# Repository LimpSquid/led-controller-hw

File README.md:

# Next revision
- Pull-ups (10k) on TLC5940 outputs.
- Pull-ups on MOSFET gates need to be lowered to 1k.
- Add 47nF capacitors on drain (output) of MOSFETs to reduce noise.

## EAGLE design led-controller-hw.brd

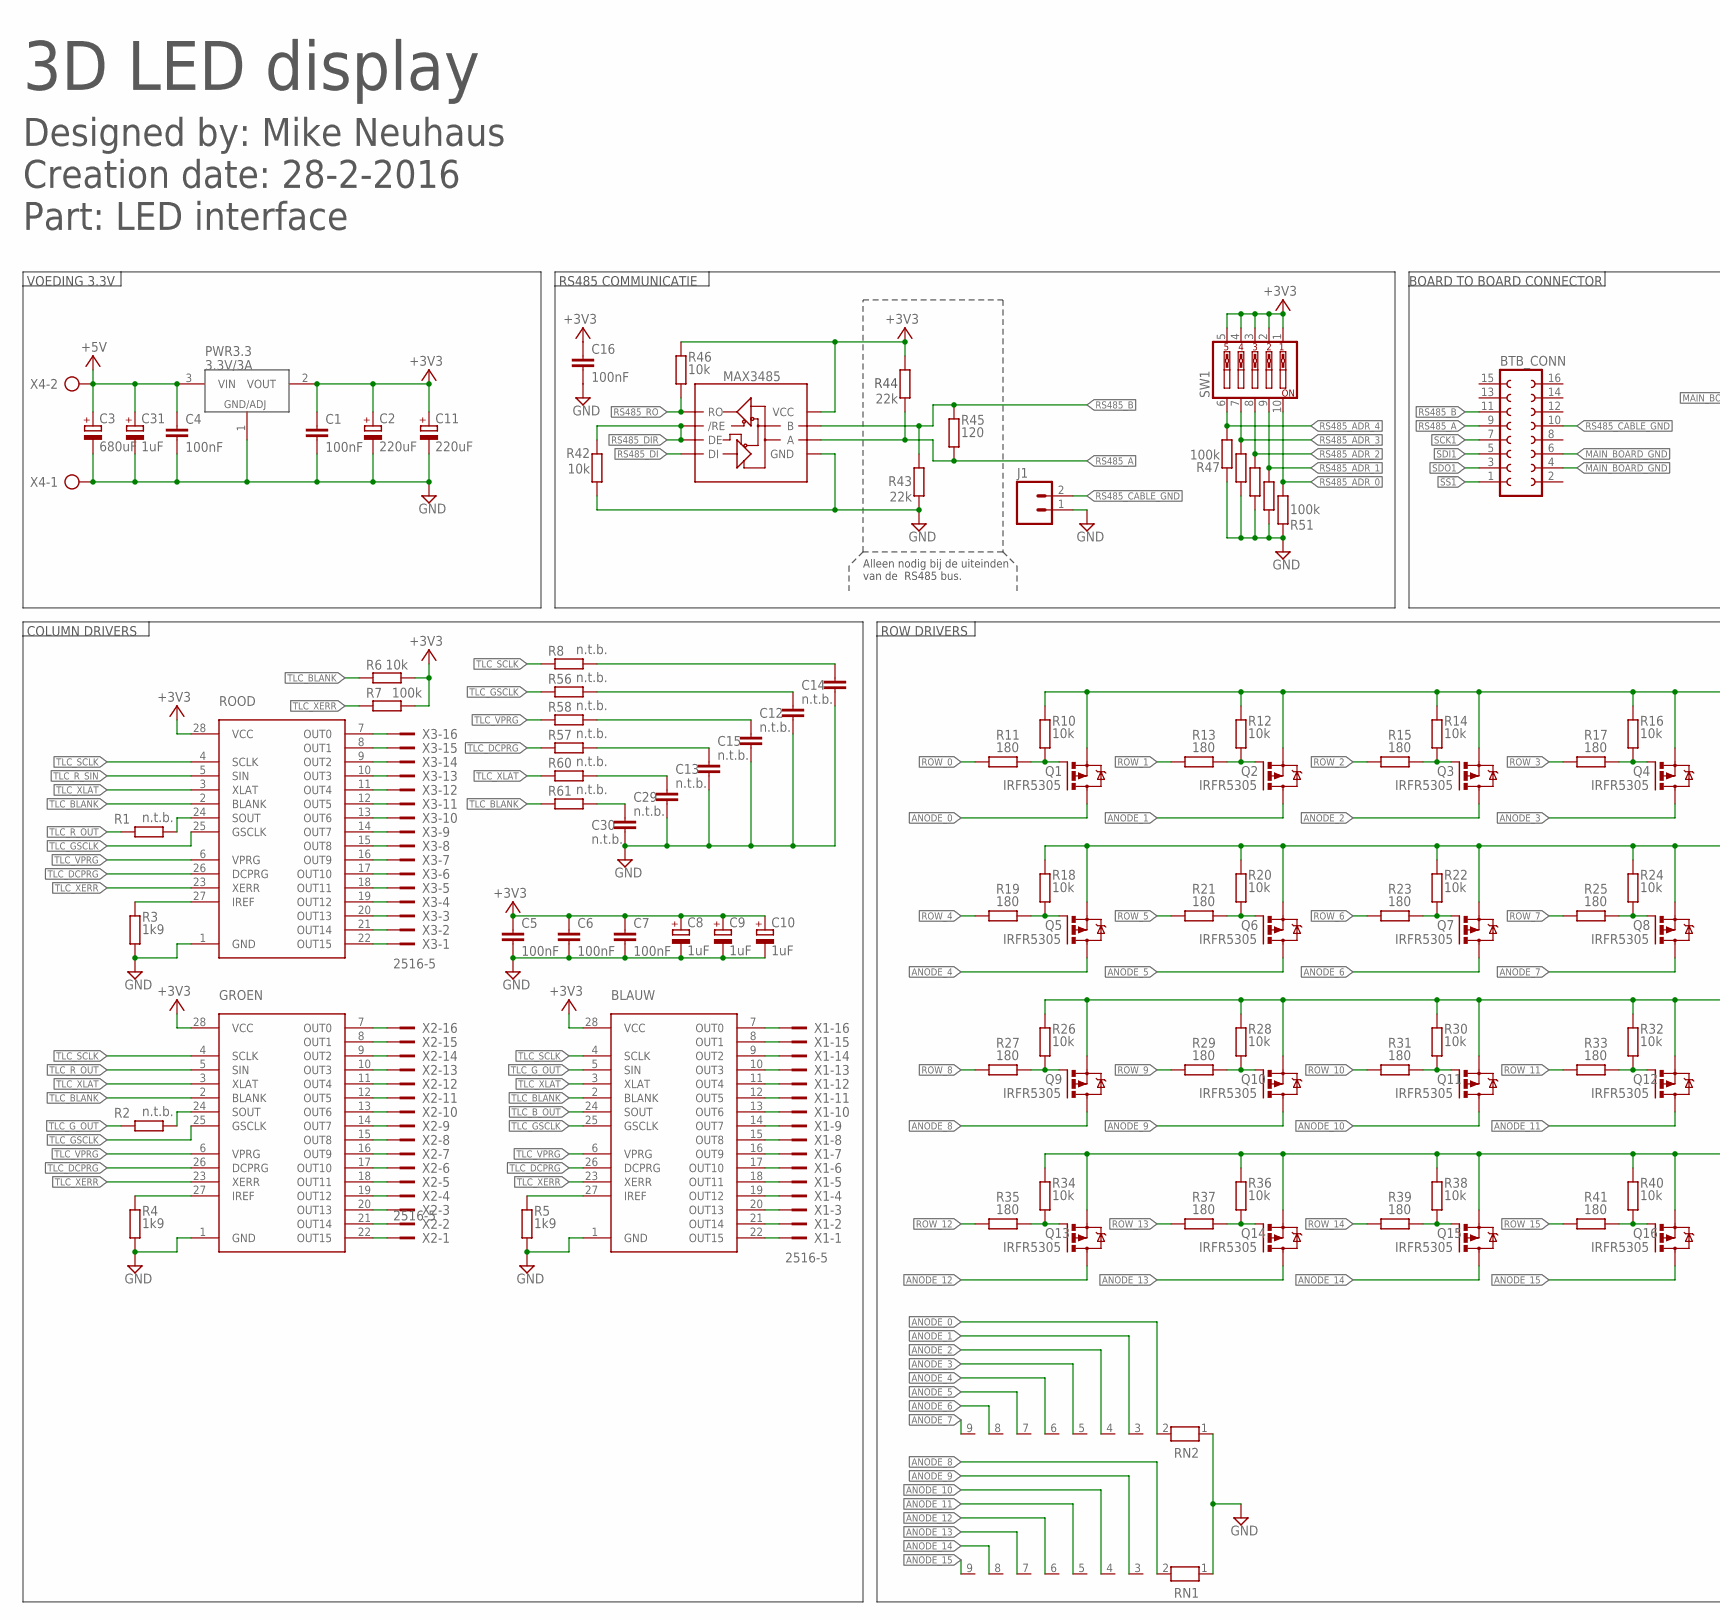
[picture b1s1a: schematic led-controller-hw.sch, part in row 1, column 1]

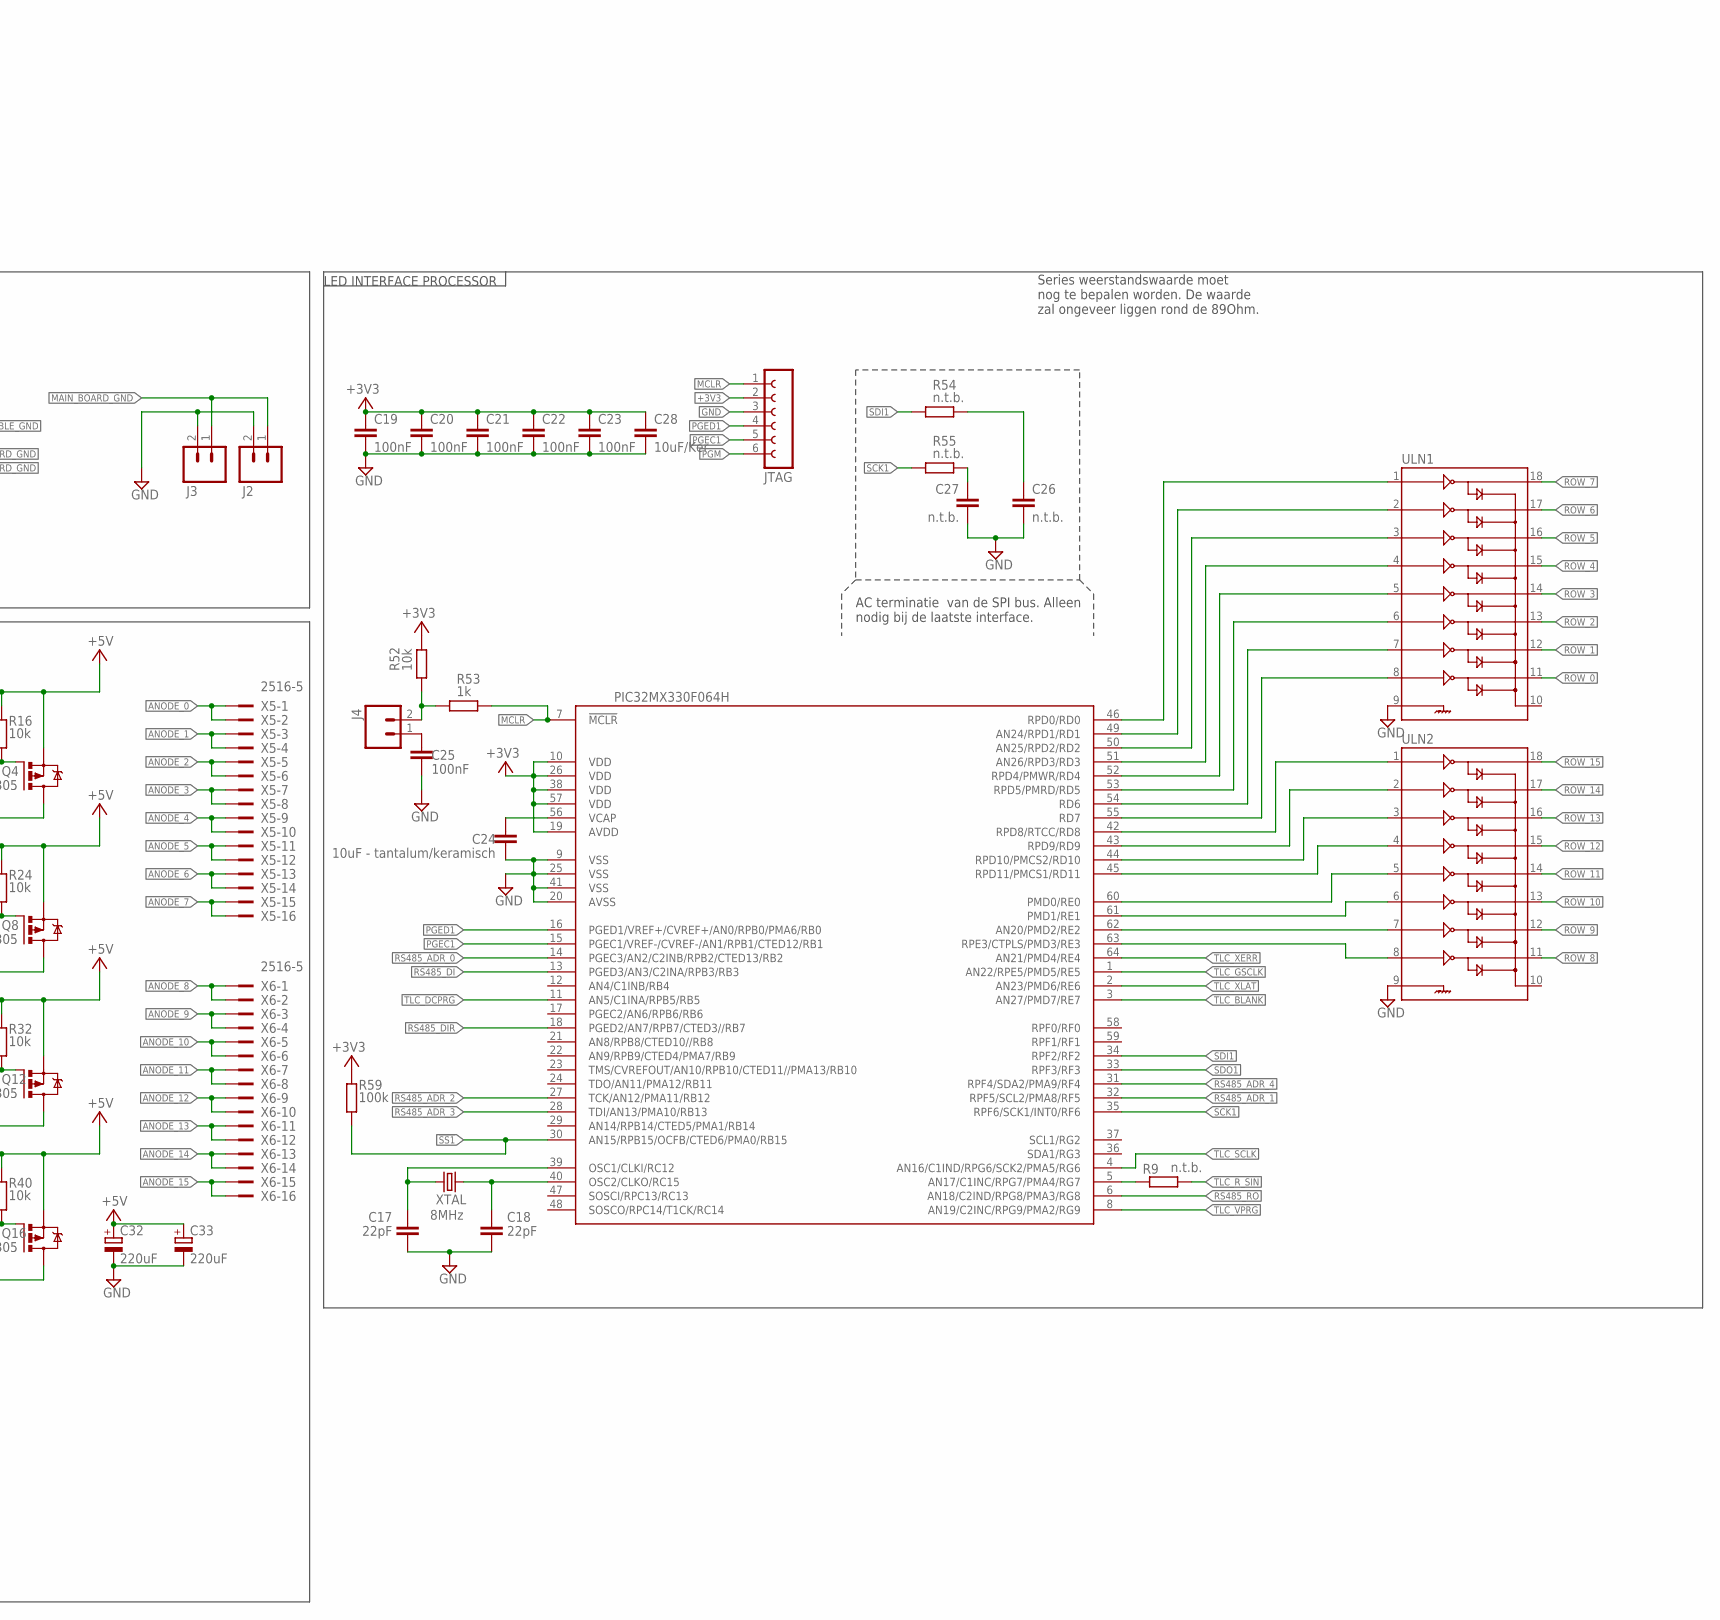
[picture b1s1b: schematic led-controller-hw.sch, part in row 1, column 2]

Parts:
BLAUW: TLC5940PWPR; TSSOP-28-PWP
BTB_CONN: FE08-2W
C1, C4, C5, C6, C7, C16, C19, C20, C21, C22, C23, C25: 100nF; C0805
C2, C11, C32, C33: 220uF; E2,5-6E
C3: 680uF; CPOL_EU10-27
C8, C9, C10, C31: 1uF; E2,5-5
C12, C13, C14, C15, C26, C27, C29, C30: n.t.b.; C0805
C17, C18: 22pF; C0805
C24: 10uF - tantalum/keramisch; C0805
C28: 10uF/Ker; C0805
GROEN: TLC5940PWPR; TSSOP-28-PWP
J1, J2, J3, J4: M02LOCK; 1X02_LOCK
JTAG: FE06-1; FE06
MAX3485: RS485SOIC; SO08
PIC32MX330F064H: PIC32MX330F064H; TQFP-64-10
PWR3.3: 3.3V/3A; TO-220
Q1, Q2, Q3, Q4, Q5, Q6, Q7, Q8, Q9, Q10, Q11, Q12, Q13, Q14, Q15, Q16: IRFR5305; D-PAK_TO252AA
R1, R2, R8, R9, R54, R55, R56, R57, R58, R60, R61: n.t.b.; M0805
R3, R4, R5: 1k9; M0805
R6, R10, R12, R14, R16, R18, R20, R22, R24, R26, R28, R30, R32, R34, R36, R38, R40, R42, R46, R52: 10k; M0805
R7, R47, R48, R49, R50, R51, R59: 100k; M0805
R11, R13, R15, R17, R19, R21, R23, R25, R27, R29, R31, R33, R35, R37, R39, R41: 180; M0805
R43, R44: 22k; M0805
R45: 120; M0805
R53: 1k; M0805
RN1, RN2: RN08; RN-9
ROOD: TLC5940PWPR; TSSOP-28-PWP
SW1: SW_DIP-5; EDG-05
ULN1, ULN2: ULN2803SOICW; SO18L
X1, X2, X3, X5, X6: 2516-5; PAK100/2500-5-16
X4: AK500/2-H
XTAL: 8MHz; CSM-7X-DU

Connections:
!SS1: BTB_CONN.1, PIC32MX330F064H.30 (AN15/RPB15/OCFB/CTED6/PMA0/RB15), R59.2
+3V3: BLAUW.28 (VCC), C1.1, C2.+, C5.1, C6.1, C7.1, C8.+, C9.+, C10.+, C11.+, C16.1, C19.1, C20.1, C21.1, C22.1, C23.1, C28.1, GROEN.28 (VCC), JTAG.2, MAX3485.8 (VCC), PIC32MX330F064H.10 (VDD), PIC32MX330F064H.19 (AVDD), PIC32MX330F064H.26 (VDD), PIC32MX330F064H.38 (VDD), PIC32MX330F064H.57 (VDD), PWR3.3.2 (VOUT), R6.2, R7.2, R44.1, R46.2, R52.1, R59.1, ROOD.28 (VCC), SW1.1, SW1.2, SW1.3, SW1.4, SW1.5
+5V: C3.1 (+), C4.1, C31.+, C32.+, C33.+, PWR3.3.3 (VIN), Q1.3 (S), Q2.3 (S), Q3.3 (S), Q4.3 (S), Q5.3 (S), Q6.3 (S), Q7.3 (S), Q8.3 (S), Q9.3 (S), Q10.3 (S), Q11.3 (S), Q12.3 (S), Q13.3 (S), Q14.3 (S), Q15.3 (S), Q16.3 (S), R10.2, R12.2, R14.2, R16.2, R18.2, R20.2, R22.2, R24.2, R26.2, R28.2, R30.2, R32.2, R34.2, R36.2, R38.2, R40.2, X4.2
ANODE_0: Q1.4 (D), RN2.2, X5.1, X5.2
ANODE_1: Q2.4 (D), RN2.3, X5.3, X5.4
ANODE_2: Q3.4 (D), RN2.4, X5.5, X5.6
ANODE_3: Q4.4 (D), RN2.5, X5.7, X5.8
ANODE_4: Q5.4 (D), RN2.6, X5.9, X5.10
ANODE_5: Q6.4 (D), RN2.7, X5.11, X5.12
ANODE_6: Q7.4 (D), RN2.8, X5.13, X5.14
ANODE_7: Q8.4 (D), RN2.9, X5.15, X5.16
ANODE_8: Q9.4 (D), RN1.2, X6.1, X6.2
ANODE_9: Q10.4 (D), RN1.3, X6.3, X6.4
ANODE_10: Q11.4 (D), RN1.4, X6.5, X6.6
ANODE_11: Q12.4 (D), RN1.5, X6.7, X6.8
ANODE_12: Q13.4 (D), RN1.6, X6.9, X6.10
ANODE_13: Q14.4 (D), RN1.7, X6.11, X6.12
ANODE_14: Q15.4 (D), RN1.8, X6.13, X6.14
ANODE_15: Q16.4 (D), RN1.9, X6.15, X6.16
GND: BLAUW.1 (GND), C1.2, C2.-, C3.2 (-), C4.2, C5.2, C6.2, C7.2, C8.-, C9.-, C10.-, C11.-, C12.2, C13.2, C14.2, C15.2, C16.2, C17.1, C18.1, C19.2, C20.2, C21.2, C22.2, C23.2, C24.2, C25.2, C26.2, C27.2, C28.2, C29.2, C30.2, C31.-, C32.-, C33.-, GROEN.1 (GND), J1.1, J2.2, J3.2, JTAG.3, MAX3485.5 (GND), PIC32MX330F064H.9 (VSS), PIC32MX330F064H.20 (AVSS), PIC32MX330F064H.25 (VSS), PIC32MX330F064H.41 (VSS), PWR3.3.1 (GND/ADJ), R3.1, R4.1, R5.1, R42.2, R43.2, R47.1, R48.1, R49.1, R50.1, R51.1, RN1.1, RN2.1, ROOD.1 (GND), ULN1.9, ULN2.9, X4.1
MAIN_BOARD_GND: BTB_CONN.4, BTB_CONN.6, J2.1, J3.1
MCLR: JTAG.1, PIC32MX330F064H.7 (!MCLR), R53.1
unnamed: C13.1, R57.1
unnamed: Q1.1 (G), R10.1, R11.1
unnamed: R3.2, ROOD.27 (IREF)
unnamed: BLAUW.27 (IREF), R5.2
unnamed: GROEN.27 (IREF), R4.2
unnamed: ROOD.22 (OUT15), X3.1
unnamed: ROOD.21 (OUT14), X3.2
unnamed: ROOD.20 (OUT13), X3.3
unnamed: ROOD.19 (OUT12), X3.4
unnamed: ROOD.18 (OUT11), X3.5
unnamed: ROOD.17 (OUT10), X3.6
unnamed: ROOD.16 (OUT9), X3.7
unnamed: ROOD.15 (OUT8), X3.8
unnamed: ROOD.14 (OUT7), X3.9
unnamed: ROOD.13 (OUT6), X3.10
unnamed: ROOD.12 (OUT5), X3.11
unnamed: ROOD.11 (OUT4), X3.12
unnamed: ROOD.10 (OUT3), X3.13
unnamed: ROOD.9 (OUT2), X3.14
unnamed: ROOD.8 (OUT1), X3.15
unnamed: ROOD.7 (OUT0), X3.16
unnamed: GROEN.20 (OUT13), X2.3
unnamed: GROEN.22 (OUT15), X2.1
unnamed: GROEN.21 (OUT14), X2.2
unnamed: GROEN.19 (OUT12), X2.4
unnamed: GROEN.18 (OUT11), X2.5
unnamed: GROEN.17 (OUT10), X2.6
unnamed: GROEN.16 (OUT9), X2.7
unnamed: GROEN.15 (OUT8), X2.8
unnamed: GROEN.14 (OUT7), X2.9
unnamed: GROEN.13 (OUT6), X2.10
unnamed: GROEN.12 (OUT5), X2.11
unnamed: GROEN.11 (OUT4), X2.12
unnamed: GROEN.10 (OUT3), X2.13
unnamed: GROEN.9 (OUT2), X2.14
unnamed: GROEN.8 (OUT1), X2.15
unnamed: GROEN.7 (OUT0), X2.16
unnamed: BLAUW.15 (OUT8), X1.8
unnamed: BLAUW.7 (OUT0), X1.16
unnamed: BLAUW.8 (OUT1), X1.15
unnamed: BLAUW.9 (OUT2), X1.14
unnamed: BLAUW.10 (OUT3), X1.13
unnamed: BLAUW.11 (OUT4), X1.12
unnamed: BLAUW.12 (OUT5), X1.11
unnamed: BLAUW.13 (OUT6), X1.10
unnamed: BLAUW.14 (OUT7), X1.9
unnamed: BLAUW.16 (OUT9), X1.7
unnamed: BLAUW.17 (OUT10), X1.6
unnamed: BLAUW.18 (OUT11), X1.5
unnamed: BLAUW.19 (OUT12), X1.4
unnamed: BLAUW.20 (OUT13), X1.3
unnamed: BLAUW.21 (OUT14), X1.2
unnamed: BLAUW.22 (OUT15), X1.1
unnamed: C12.1, R56.1
unnamed: Q2.1 (G), R12.1, R13.1
unnamed: Q6.1 (G), R20.1, R21.1
unnamed: Q3.1 (G), R14.1, R15.1
unnamed: C18.2, PIC32MX330F064H.40 (OSC2/CLKO/RC15), XTAL.1
unnamed: Q4.1 (G), R16.1, R17.1
unnamed: C17.2, PIC32MX330F064H.39 (OSC1/CLKI/RC12), XTAL.2
unnamed: Q5.1 (G), R18.1, R19.1
unnamed: C25.1, J4.1
unnamed: Q7.1 (G), R22.1, R23.1
unnamed: J4.2, R52.2, R53.2
unnamed: C26.1, R54.1
unnamed: Q8.1 (G), R24.1, R25.1
unnamed: C27.1, R55.1
unnamed: R1.1, ROOD.24 (SOUT)
unnamed: Q9.1 (G), R26.1, R27.1
unnamed: GROEN.24 (SOUT), R2.1
unnamed: C14.1, R8.1
unnamed: Q10.1 (G), R28.1, R29.1
unnamed: C15.1, R58.1
unnamed: C29.1, R60.1
unnamed: Q11.1 (G), R30.1, R31.1
unnamed: C30.1, R61.1
unnamed: PIC32MX330F064H.5 (AN17/C1INC/RPG7/PMA4/RG7), R9.2
unnamed: Q12.1 (G), R32.1, R33.1
unnamed: PIC32MX330F064H.46 (RPD0/RD0), ULN1.1
unnamed: PIC32MX330F064H.49 (AN24/RPD1/RD1), ULN1.2
unnamed: Q13.1 (G), R34.1, R35.1
unnamed: PIC32MX330F064H.50 (AN25/RPD2/RD2), ULN1.3
unnamed: PIC32MX330F064H.51 (AN26/RPD3/RD3), ULN1.4
unnamed: Q14.1 (G), R36.1, R37.1
unnamed: PIC32MX330F064H.52 (RPD4/PMWR/RD4), ULN1.5
unnamed: PIC32MX330F064H.53 (RPD5/PMRD/RD5), ULN1.6
unnamed: Q15.1 (G), R38.1, R39.1
unnamed: PIC32MX330F064H.54 (RD6), ULN1.7
unnamed: PIC32MX330F064H.55 (RD7), ULN1.8
unnamed: Q16.1 (G), R40.1, R41.1
unnamed: PIC32MX330F064H.42 (RPD8/RTCC/RD8), ULN2.1
unnamed: PIC32MX330F064H.43 (RPD9/RD9), ULN2.2
unnamed: PIC32MX330F064H.44 (RPD10/PMCS2/RD10), ULN2.3
unnamed: PIC32MX330F064H.45 (RPD11/PMCS1/RD11), ULN2.4
unnamed: PIC32MX330F064H.60 (PMD0/RE0), ULN2.5
unnamed: PIC32MX330F064H.61 (PMD1/RE1), ULN2.6
unnamed: PIC32MX330F064H.62 (AN20/PMD2/RE2), ULN2.7
unnamed: PIC32MX330F064H.63 (RPE3/CTPLS/PMD3/RE3), ULN2.8
PGEC1: JTAG.5, PIC32MX330F064H.15 (PGEC1/VREF-/CVREF-/AN1/RPB1/CTED12/RB1)
PGED1: JTAG.4, PIC32MX330F064H.16 (PGED1/VREF+/CVREF+/AN0/RPB0/PMA6/RB0)
PGM: JTAG.6
ROW_0: R11.2, ULN1.11
ROW_1: R13.2, ULN1.12
ROW_2: R15.2, ULN1.13
ROW_3: R17.2, ULN1.14
ROW_4: R19.2, ULN1.15
ROW_5: R21.2, ULN1.16
ROW_6: R23.2, ULN1.17
ROW_7: R25.2, ULN1.18
ROW_8: R27.2, ULN2.11
ROW_9: R29.2, ULN2.12
ROW_10: R31.2, ULN2.13
ROW_11: R33.2, ULN2.14
ROW_12: R35.2, ULN2.15
ROW_13: R37.2, ULN2.16
ROW_14: R39.2, ULN2.17
ROW_15: R41.2, ULN2.18
RS485_A: BTB_CONN.9, MAX3485.6 (A), R44.2, R45.1
RS485_ADR_0: PIC32MX330F064H.14 (PGEC3/AN2/C2INB/RPB2/CTED13/RB2), R51.2, SW1.10
RS485_ADR_1: PIC32MX330F064H.32 (RPF5/SCL2/PMA8/RF5), R50.2, SW1.9
RS485_ADR_2: PIC32MX330F064H.27 (TCK/AN12/PMA11/RB12), R49.2, SW1.8
RS485_ADR_3: PIC32MX330F064H.28 (TDI/AN13/PMA10/RB13), R48.2, SW1.7
RS485_ADR_4: PIC32MX330F064H.31 (RPF4/SDA2/PMA9/RF4), R47.2, SW1.6
RS485_B: BTB_CONN.11, MAX3485.7 (B), R43.1, R45.2
RS485_CABLE_GND: BTB_CONN.10, J1.2
RS485_DI: MAX3485.4 (DI), PIC32MX330F064H.13 (PGED3/AN3/C2INA/RPB3/RB3)
RS485_DIR: MAX3485.2 (/RE), MAX3485.3 (DE), PIC32MX330F064H.18 (PGED2/AN7/RPB7/CTED3//RB7), R42.1
RS485_RO: MAX3485.1 (RO), PIC32MX330F064H.6 (AN18/C2IND/RPG8/PMA3/RG8), R46.1
SCK1: BTB_CONN.7, PIC32MX330F064H.35 (RPF6/SCK1/INT0/RF6), R55.2
SDI1: BTB_CONN.5, PIC32MX330F064H.34 (RPF2/RF2), R54.2
SDO1: BTB_CONN.3, PIC32MX330F064H.33 (RPF3/RF3)
TLC_BLANK: BLAUW.2 (BLANK), GROEN.2 (BLANK), PIC32MX330F064H.3 (AN27/PMD7/RE7), R6.1, R61.2, ROOD.2 (BLANK)
TLC_B_OUT: BLAUW.24 (SOUT)
TLC_DCPRG: BLAUW.26 (DCPRG), GROEN.26 (DCPRG), PIC32MX330F064H.11 (AN5/C1INA/RPB5/RB5), R57.2, ROOD.26 (DCPRG)
TLC_GSCLK: BLAUW.25 (GSCLK), GROEN.25 (GSCLK), PIC32MX330F064H.1 (AN22/RPE5/PMD5/RE5), R56.2, ROOD.25 (GSCLK)
TLC_G_OUT: BLAUW.5 (SIN), R2.2
TLC_R_OUT: GROEN.5 (SIN), R1.2
TLC_R_SIN: R9.1, ROOD.5 (SIN)
TLC_SCLK: BLAUW.4 (SCLK), GROEN.4 (SCLK), PIC32MX330F064H.4 (AN16/C1IND/RPG6/SCK2/PMA5/RG6), R8.2, ROOD.4 (SCLK)
TLC_VPRG: BLAUW.6 (VPRG), GROEN.6 (VPRG), PIC32MX330F064H.8 (AN19/C2INC/RPG9/PMA2/RG9), R58.2, ROOD.6 (VPRG)
TLC_XERR: BLAUW.23 (XERR), GROEN.23 (XERR), PIC32MX330F064H.64 (AN21/PMD4/RE4), R7.1, ROOD.23 (XERR)
TLC_XLAT: BLAUW.3 (XLAT), GROEN.3 (XLAT), PIC32MX330F064H.2 (AN23/PMD6/RE6), R60.2, ROOD.3 (XLAT)
VCAP: C24.1, PIC32MX330F064H.56 (VCAP)

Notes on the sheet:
VOEDING 3.3V
COLUMN DRIVERS
ROW DRIVERS
Alleen nodig bij de uiteinden van de RS485 bus.
RS485 COMMUNICATIE
AC terminatie van de SPI bus. Alleen nodig bij de laatste interface.
BOARD TO BOARD CONNECTOR
LED INTERFACE PROCESSOR
Series weerstandswaarde moet nog te bepalen worden. De waarde zal ongeveer liggen rond de 89Ohm.
3D LED display
Designed by: Mike Neuhaus Creation date: 28-2-2016 Part: LED interface

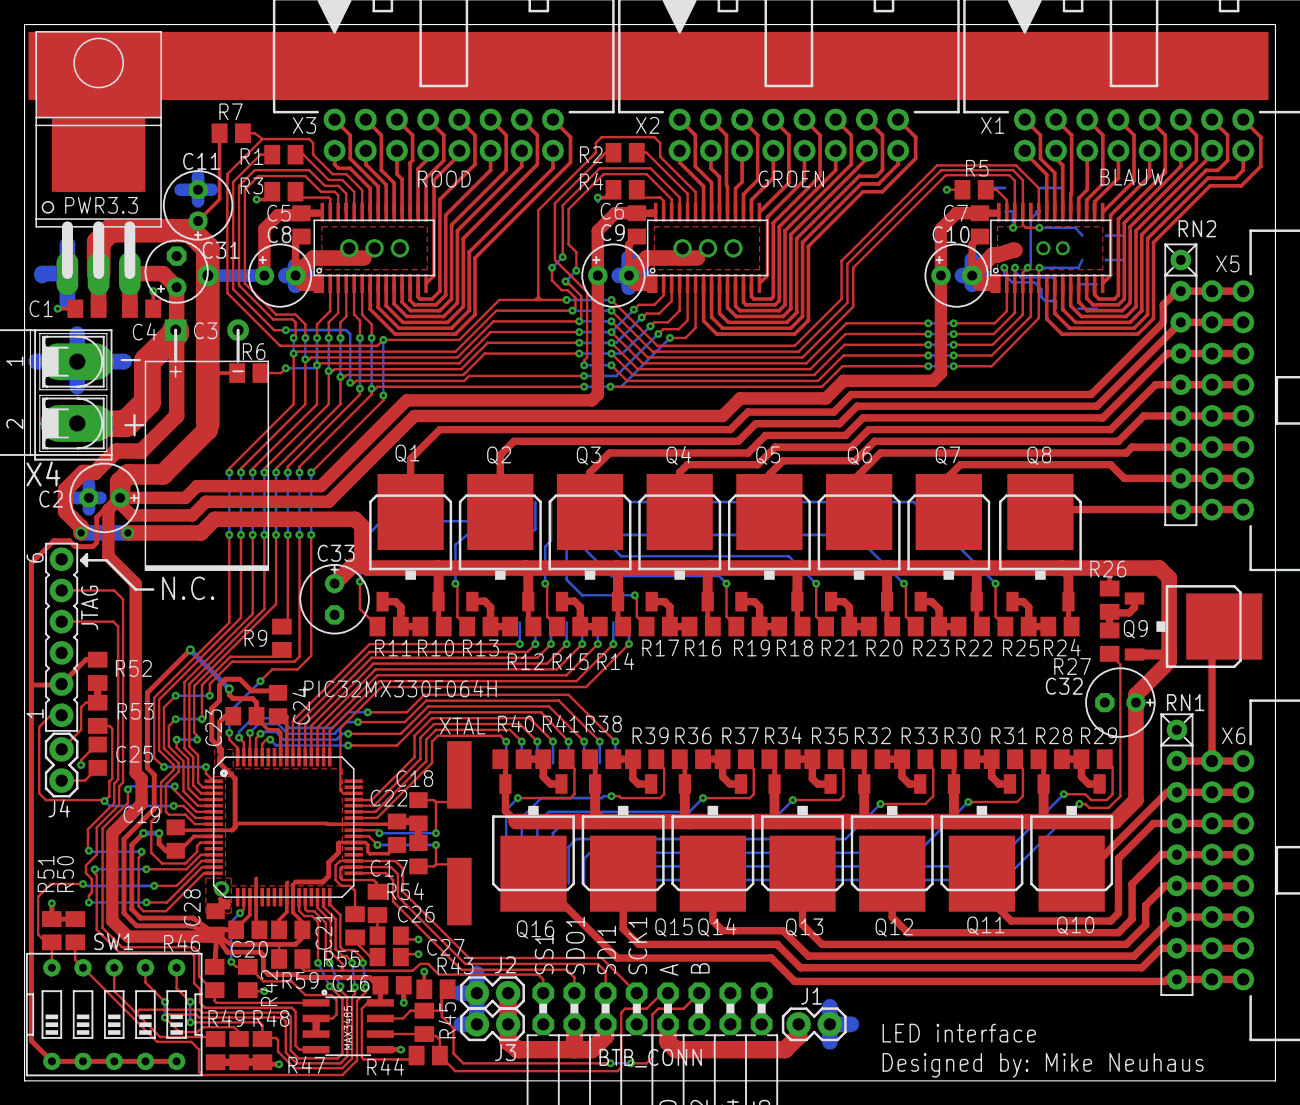
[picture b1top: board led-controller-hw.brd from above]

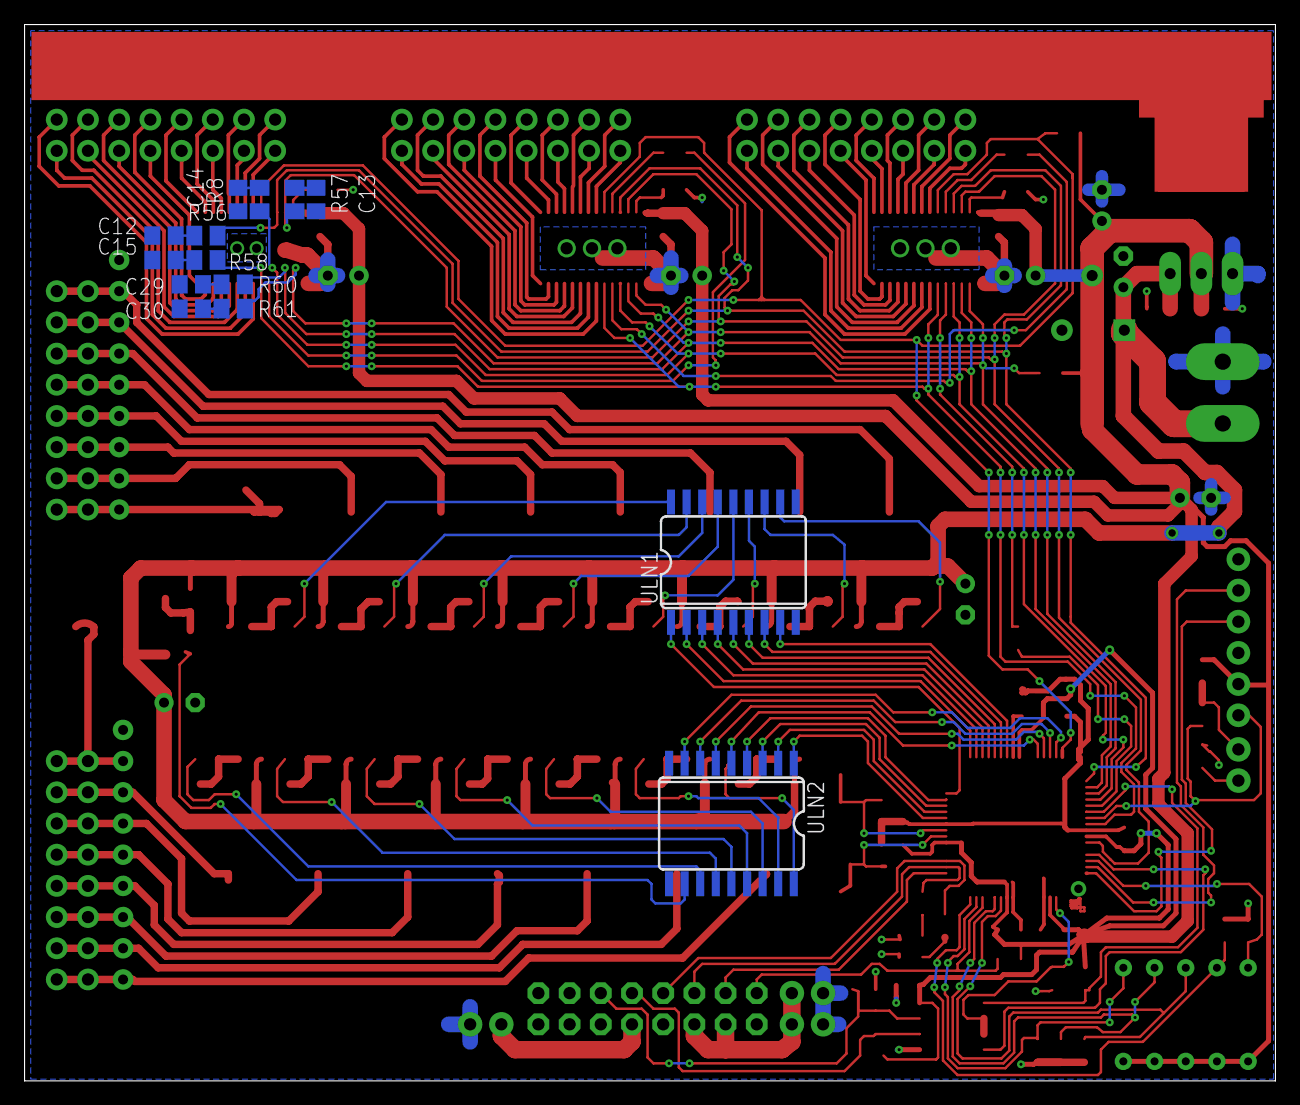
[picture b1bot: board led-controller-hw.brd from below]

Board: 2 copper layers, 101.8 x 86.0 mm, 134 parts (14 on the bottom side), 163 nets.

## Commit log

2024-02-07 A:Wdded readme
2024-02-07 Create LICENSE

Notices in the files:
parts and their libraries:
SparkFun-Connectors: Licensing: Creative Commons ShareAlike 4.0 International - https://creativecommons.org/licenses/by-sa/4.0
